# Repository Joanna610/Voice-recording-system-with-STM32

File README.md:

# Voice-recording-system-with-STM32

Not sophisticated project of voice recording implementation. The project is based on the microcontroller STM32F3, which reads the data from the microphone and sends it to the speaker. It is supposed to communicate by SPI with the microSD card reader, which was supposed to store the recorded data.

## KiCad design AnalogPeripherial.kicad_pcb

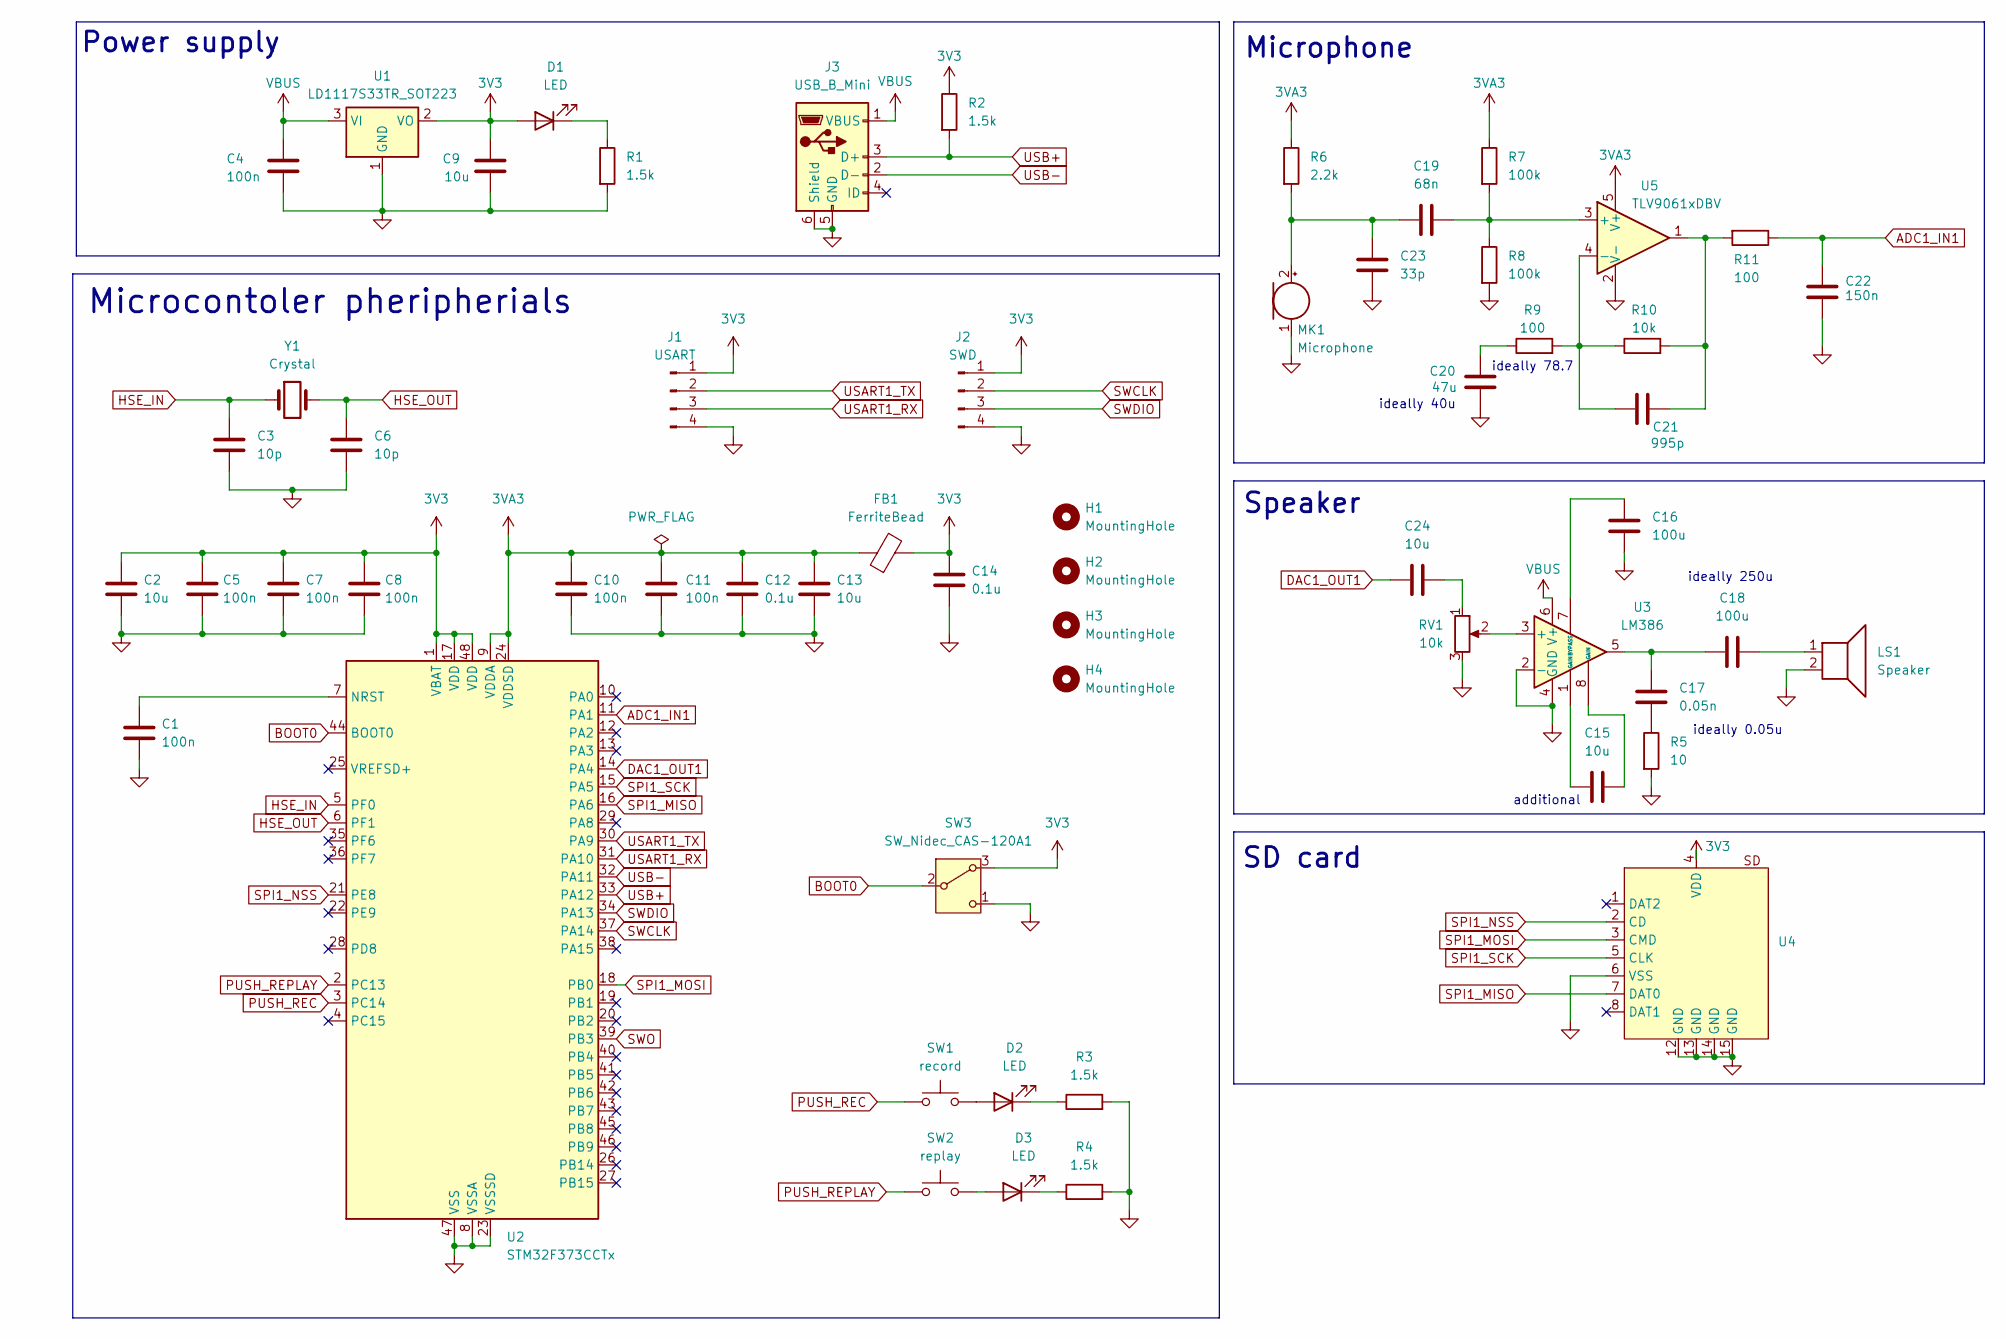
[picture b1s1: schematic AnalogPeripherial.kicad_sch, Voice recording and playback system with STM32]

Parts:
C1, C4, C5, C7, C8, C10, C11: 100n; C_0805_2012Metric_Pad1.18x1.45mm_HandSolder
C2, C9, C13, C15, C24: 10u; C_0805_2012Metric_Pad1.18x1.45mm_HandSolder
C3, C6: 10p; C_0805_2012Metric_Pad1.18x1.45mm_HandSolder
C12, C14: 0.1u; C_0805_2012Metric_Pad1.18x1.45mm_HandSolder
C16, C18: 100u; C_0805_2012Metric_Pad1.18x1.45mm_HandSolder
C17: 0.05n; C_0805_2012Metric_Pad1.18x1.45mm_HandSolder
C19: 68n; C_0805_2012Metric_Pad1.18x1.45mm_HandSolder
C20: 47u; C_0805_2012Metric_Pad1.18x1.45mm_HandSolder
C21: 995p; C_0805_2012Metric_Pad1.18x1.45mm_HandSolder
C22: 150n; C_0805_2012Metric_Pad1.18x1.45mm_HandSolder
C23: 33p; C_0805_2012Metric_Pad1.18x1.45mm_HandSolder
D1, D2, D3: LED; LED_0805_2012Metric_Pad1.15x1.40mm_HandSolder
FB1: FerriteBead; L_0805_2012Metric_Pad1.05x1.20mm_HandSolder
H1, H2, H3, H4: MountingHole; MountingHole_2.2mm_M2
J1: USART; PinHeader_1x04_P2.54mm_Vertical
J2: SWD; PinHeader_1x04_P2.54mm_Vertical
J3: USB_B_Mini; USB_Mini-B_Lumberg_2486_01_Horizontal
LS1: Speaker; speaker
MK1: Microphone; microphone
R1, R2, R3, R4: 1.5k; R_0805_2012Metric_Pad1.20x1.40mm_HandSolder
R5: 10; R_0805_2012Metric_Pad1.20x1.40mm_HandSolder
R6: 2.2k; R_0805_2012Metric_Pad1.20x1.40mm_HandSolder
R7, R8: 100k; R_0805_2012Metric_Pad1.20x1.40mm_HandSolder
R9, R11: 100; R_0805_2012Metric_Pad1.20x1.40mm_HandSolder
R10: 10k; R_0805_2012Metric_Pad1.20x1.40mm_HandSolder
RV1: 10k; potencjometr
SW1: record; button
SW2: replay; button
SW3: SW_Nidec_CAS-120A1; Nidec_Copal_CAS-120A
U1: LD1117S33TR_SOT223; SOT-223-3_TabPin2
U2: STM32F373CCTx; LQFP-48_7x7mm_P0.5mm
U3: LM386; PowerIntegrations_SO-8
U4: microSD
U5: TLV9061xDBV; SOT-23-5
Y1: Crystal; Crystal_HC49-4H_Vertical

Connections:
3V3: C2.1, C5.1, C7.1, C8.1, C9.1, C14.1, D1.2 (A), FB1.2, J1.1, J2.1, R2.1, SW3.3 (A), U1.2 (VO), U2.1 (VBAT), U2.17 (VDD), U2.48 (VDD), U4.4 (VDD)
3VA3: C10.1, C11.1, C12.1, C13.1, FB1.1, R6.1, R7.1, U2.9 (VDDA), U2.24 (VDDSD), U5.5 (V+)
ADC1_IN1: C22.2, R11.1, U2.11 (PA1)
BOOT0: SW3.2 (B), U2.44 (BOOT0)
DAC1_OUT1: C24.1, U2.14 (PA4)
GND: C1.2, C2.2, C3.2, C4.2, C5.2, C6.2, C7.2, C8.2, C9.2, C10.2, C11.2, C12.2, C13.2, C14.2, C16.1, C20.1, C22.1, C23.1, J1.4, J2.4, J3.5 (GND), J3.6 (Shield), LS1.2, MK1.1 (-), R1.2, R3.2, R4.2, R5.2, R8.2, RV1.3, SW3.1 (C), U1.1 (GND), U2.8 (VSSA), U2.23 (VSSSD), U2.47 (VSS), U3.2 (-), U3.4 (GND), U4.6 (VSS), U4.12 (GND), U4.13 (GND), U4.14 (GND), U4.15 (GND), U5.2 (V-)
HSE_IN: C3.1, U2.5 (PF0), Y1.1
HSE_OUT: C6.1, U2.6 (PF1), Y1.2
unnamed: C15.1, U3.1 (GAIN)
unnamed: C15.2, U3.8 (GAIN)
unnamed: C17.1, C18.1, U3.5
unnamed: C17.2, R5.1
unnamed: C18.2, LS1.1
unnamed: C20.2, R9.1
unnamed: C21.2, R10.2, R11.2, U5.1
unnamed: C24.2, RV1.1
unnamed: D1.1 (K), R1.1
unnamed: D2.2 (A), SW1.2
unnamed: D2.1 (K), R3.1
unnamed: D3.2 (A), SW2.2
unnamed: D3.1 (K), R4.1
unnamed: C19.1, C23.2, MK1.2 (+), R6.2
unnamed: C1.1, U2.7 (NRST)
unnamed: RV1.2, U3.3 (+)
unnamed: C16.2, U3.7 (BYPASS)
unnamed: C19.2, R7.2, R8.1, U5.3 (+)
unnamed: C21.1, R9.2, R10.1, U5.4 (-)
PUSH_REC: SW1.1, U2.3 (PC14)
PUSH_REPLAY: SW2.1, U2.2 (PC13)
SPI1_MISO: U2.16 (PA6), U4.7 (DAT0)
SPI1_MOSI: U2.18 (PB0), U4.3 (CMD)
SPI1_NSS: U2.21 (PE8), U4.2 (CD)
SPI1_SCK: U2.15 (PA5), U4.5 (CLK)
SWCLK: J2.2, U2.37 (PA14)
SWDIO: J2.3, U2.34 (PA13)
USART1_RX: J1.3, U2.31 (PA10)
USART1_TX: J1.2, U2.30 (PA9)
USB+: J3.3 (D+), R2.2, U2.33 (PA12)
USB-: J3.2 (D-), U2.32 (PA11)
VBUS: C4.1, J3.1 (VBUS), U1.3 (VI), U3.6 (V+)

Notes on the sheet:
Microphone
Microcontoler pheripherials
Speaker
additional
Power supply
SD card
ideally 40u
ideally 250u
ideally 78.7
ideally 0.05u

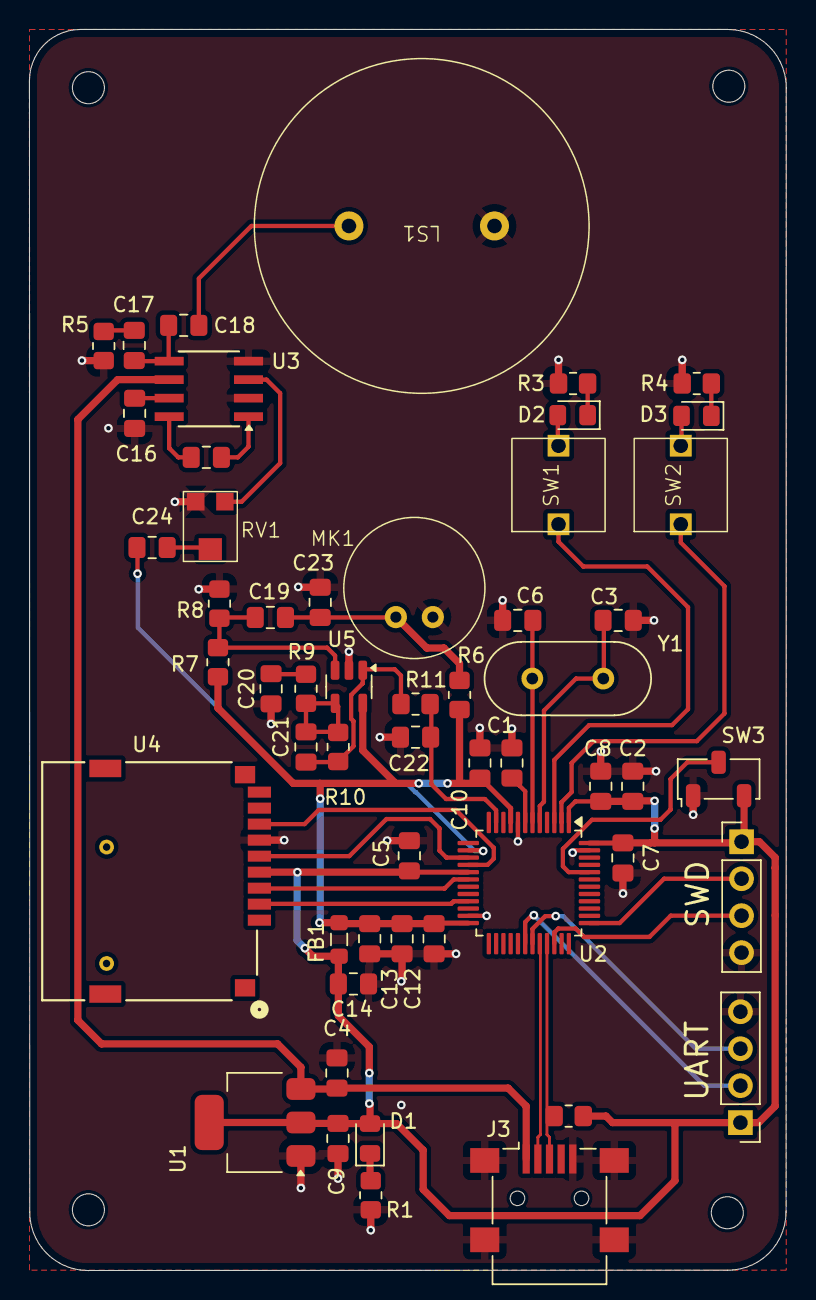
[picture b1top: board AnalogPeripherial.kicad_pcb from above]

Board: 2 copper layers, 52.0 x 85.3 mm, 58 parts (0 on the bottom side), 40 nets.

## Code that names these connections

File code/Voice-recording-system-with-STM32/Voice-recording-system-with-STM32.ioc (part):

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Mcu.Name=STM32F373C(8-B-C)Tx
Mcu.Package=LQFP48
Mcu.UserName=STM32F373CCTx
PA1.Mode=IN1
PA1.Signal=ADC1_IN1
PA10.Mode=Asynchronous
PA10.Signal=USART1_RX
PA13.Mode=Trace_Asynchronous_SW
PA13.Signal=SYS_JTMS-SWDIO
PA14.Mode=Trace_Asynchronous_SW
PA14.Signal=SYS_JTCK-SWCLK
PA4.Signal=COMP_DAC11_group
PA5.Mode=Full_Duplex_Master
PA5.Signal=SPI1_SCK
PA6.Mode=Full_Duplex_Master
PA6.Signal=SPI1_MISO
PA9.Mode=Asynchronous
PA9.Signal=USART1_TX
PB0.Mode=Full_Duplex_Master
PB0.Signal=SPI1_MOSI
PB3.Mode=Trace_Asynchronous_SW
PB3.Signal=SYS_JTDO-TRACESWO
PC13.GPIOParameters=GPIO_PuPd,GPIO_Label
PC13.GPIO_Label=REPLAY
PC13.GPIO_PuPd=GPIO_PULLUP
PC13.Signal=GPIO_Input
PC14-OSC32_IN.GPIOParameters=GPIO_PuPd,GPIO_Label
PC14-OSC32_IN.GPIO_Label=REC
PC14-OSC32_IN.GPIO_PuPd=GPIO_PULLUP
PC14-OSC32_IN.Signal=GPIO_Input
PE8.GPIOParameters=GPIO_Speed,PinState,GPIO_Label
PE8.GPIO_Label=CS
PE8.GPIO_Speed=GPIO_SPEED_FREQ_HIGH
PE8.PinState=GPIO_PIN_SET
PE8.Signal=GPIO_Output
PF0-OSC_IN.Mode=HSE-External-Oscillator
PF0-OSC_IN.Signal=RCC_OSC_IN
PF1-OSC_OUT.Mode=HSE-External-Oscillator
PF1-OSC_OUT.Signal=RCC_OSC_OUT
RCC.HSEPLLFreq_Value=8000000
RCC.HSE_VALUE=16000000
RCC.SYSCLKFreq_VALUE=72000000
RCC.SYSCLKSource=RCC_SYSCLKSOURCE_PLLCLK
board=custom

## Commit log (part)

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2025-11-07 First sketch of project
2025-12-03 Almost finished schemat design
2025-12-03 Removing unused file
2025-12-11 Almost finish schematic
2025-12-12 Removing buffor and add some new peripherials to stm32
2025-12-13 Symulation microphone update, also peripherail correction with cubeIDE
2025-12-23 New footprint design: microphone, speaker and push button
2025-12-28 First stage of PCB design
2026-01-01 Add all footprint To do: 1. Add footprint and symbol to SD Card 2. Correct footprints and symobols 3. Finish the PCB design
2026-01-03 PCB progress
2026-02-13 PCB design still in progress
2026-02-24 Update KiCad PCB and add backup files
2026-02-24 Finished model of PCB
2026-04-02 PCB design finished
2026-04-03 Order all files and folders
2026-04-04 Small changes in values of components
2026-04-04 Start working on code
